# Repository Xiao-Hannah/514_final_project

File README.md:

# 514_final_project
# Final Project: Smart Cat Litter Box

## Project Overview

The sensing device includes a dust-proof enclosure with a load cell (pressure sensor) to measure waste levels, and I might add an air quality sensor to detect odors like ammonia to enhance its functionality. The display device uses a stepper motor-driven gauge needle to visually show cleanliness status (Clean, Needs Attention, Dirty), and a red LED lights up when it’s time to clean.

---

## Sensor Device
The sensor device consists of a load cell (5 kg) connected to an HX711 amplifier module to measure the weight of the litter box contents. The load cell detects changes in pressure caused by waste and sends analog signals to the HX711, which converts them into digital data. This data is processed by the microcontroller (e.g., ESP32 or Arduino), which calculates the cleanliness status and transmits it via Bluetooth to the display system.

Detailed sketch of the sensor device.

---

## Display Device
The display device features a stepper motor-driven gauge needle that visually indicates the cleanliness status (Clean, Needs Attention, Dirty) and an LED that lights up when the litter box requires cleaning. The TB6612 motor driver receives control signals from the display microcontroller to drive the stepper motor. Additionally, the microcontroller directly controls the LED based on the cleanliness data received via Bluetooth from the sensor microcontroller.

Detailed sketch of the display device.

---

## Data Sheets
[HX711 Datasheet](datasheets/HX711.pdf)

[TB6612 Motor Driver Datasheet](datasheets/TB6612%20Motor%20Driver.pdf)

[ESP32 Datasheet](datasheets/ESP32.pdf)

---

## Communication and System Workflow

### Communication Diagram
This figure shows how the sensor device and display device communicate via Bluetooth. The sensor device collects data from the load cell, processes it with the microcontroller, and sends the cleanliness status wirelessly to the display device.

Diagram showing communication between the sensor and display devices.

### Circuit Diagram
This detailed diagram shows how all components are physically connected. The load cell is wired to the HX711, which connects to the microcontroller. The display device includes connections between the microcontroller, motor driver, stepper motor, and LED.

Detailed circuit diagram of the Smart Pet Litter Box.

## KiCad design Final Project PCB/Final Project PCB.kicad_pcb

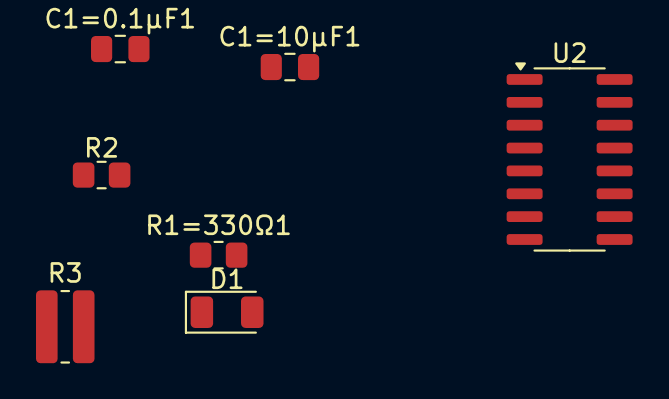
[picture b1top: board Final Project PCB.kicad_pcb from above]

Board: 2 copper layers, 7 parts (0 on the bottom side), 2 nets, no tracks yet.

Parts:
C1=0.1µF1, C1=10µF1: C; C_0805_2012Metric_Pad1.18x1.45mm_HandSolder
D1: IR26-21C_L110_TR8; LED_1206_3216Metric
R1=330Ω1: R; R_0805_2012Metric_Pad1.20x1.40mm_HandSolder
R2: R=100Ω; R_0805_2012Metric_Pad1.20x1.40mm_HandSolder
R3: R=100Ω; R_0815_2038Metric_Pad1.20x4.05mm_HandSolder
U2: HX711; SOP-16_3.9x9.9mm_P1.27mm

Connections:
GND: C1=0.1µF1.1, C1=10µF1.1, D1.1 (K)
unnamed: D1.2 (A), R1=330Ω1.2

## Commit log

2025-01-19 Created 'images' folder for storing project images.
2025-01-19 Update README.md
    Updated README with images
2025-01-19 Add files via upload
    Added updated images for circuit and flow diagram.
2025-01-19 Update README.md
    Updated circuit and flow diagram references in README
2025-01-21 Add files via upload
    Added updated circuit diagram.
2025-01-21 Create .gitkeep
    Created datasheets folder for component datasheets.
2025-01-21 Add files via upload
    Uploaded HX711 & TB6612 datasheet.
2025-01-21 Rename circuit.jpg to Circuit Diagram.jpg
2025-01-21 Rename TB6612FNG.pdf to TB6612 Motor Driver.pdf
2025-01-21 Rename hx711_datasheet.pdf to HX711.pdf
2025-01-21 Update README.md
    Updated README with new circuit diagram and datasheet links.
2025-03-11 Create Sensor
2025-03-11 Create Sensor Code
2025-03-11 Create Motor Code
